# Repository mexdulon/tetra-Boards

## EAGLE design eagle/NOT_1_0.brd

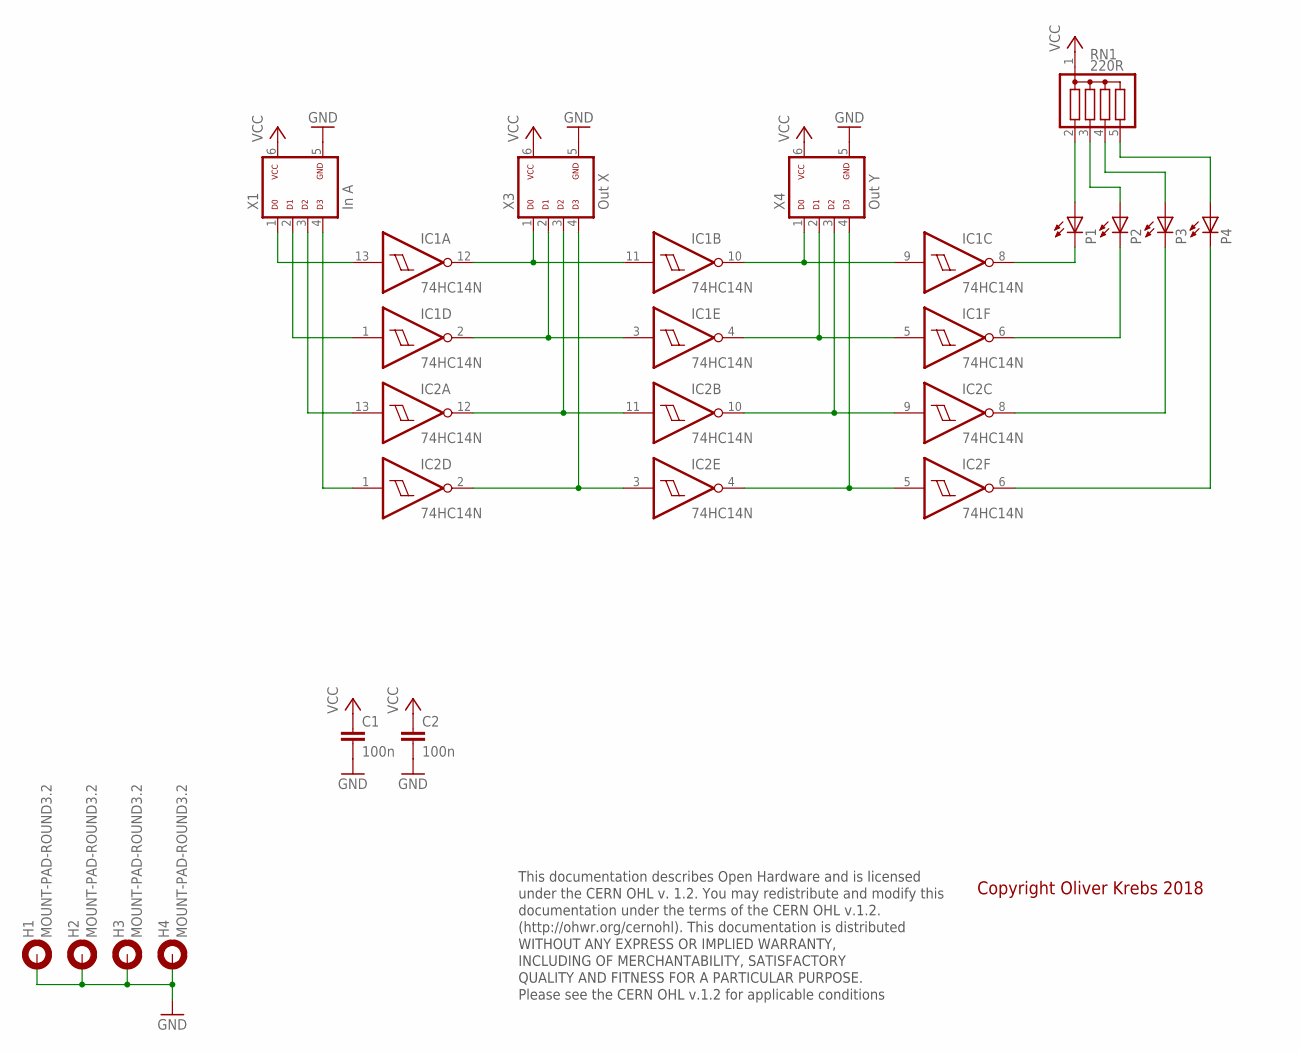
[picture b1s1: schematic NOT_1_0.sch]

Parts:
C1, C2: 100n; C050-025X075
H1, H2, H3, H4: MOUNT-PAD-ROUND3.2; 3,2-PAD
IC1, IC2: 74HC14N; DIL14
P1, P2, P3, P4: LED3MM
RN1: 220R; SIL5
X1: In A; ML-6
X3: Out X; ML-6
X4: Out Y; ML-6

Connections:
GND: C1.2, C2.2, H1.B3,2, H2.B3,2, H3.B3,2, H4.B3,2, IC1.7 (GND), IC2.7 (GND), X1.5, X3.5, X4.5
unnamed: IC1.8 (O), P1.K (C)
unnamed: IC1.6 (O), P2.K (C)
unnamed: IC2.8 (O), P3.K (C)
unnamed: IC2.6 (O), P4.K (C)
unnamed: IC1.9 (I), IC1.10 (O), X4.1
unnamed: IC1.4 (O), IC1.5 (I), X4.2
unnamed: IC2.9 (I), IC2.10 (O), X4.3
unnamed: IC2.4 (O), IC2.5 (I), X4.4
unnamed: IC1.13 (I), X1.1
unnamed: IC1.11 (I), IC1.12 (O), X3.1
unnamed: IC1.2 (O), IC1.3 (I), X3.2
unnamed: IC1.1 (I), X1.2
unnamed: IC2.13 (I), X1.3
unnamed: IC2.11 (I), IC2.12 (O), X3.3
unnamed: IC2.1 (I), X1.4
unnamed: IC2.2 (O), IC2.3 (I), X3.4
unnamed: P1.A, RN1.2
unnamed: P2.A, RN1.3
unnamed: P3.A, RN1.4
unnamed: P4.A, RN1.5
VCC: C1.1, C2.1, IC1.14 (VCC), IC2.14 (VCC), RN1.1, X1.6, X3.6, X4.6

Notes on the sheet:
This documentation describes Open Hardware and is licensed under the CERN OHL v. 1.2. You may redistribute and modify this documentation under the terms of the CERN OHL v.1.2. (http://ohwr.org/cernohl). This documentation is distributed WITHOUT ANY EXPRESS OR IMPLIED WARRANTY, INCLUDING OF MERCHANT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
Copyright Oliver Krebs 2018

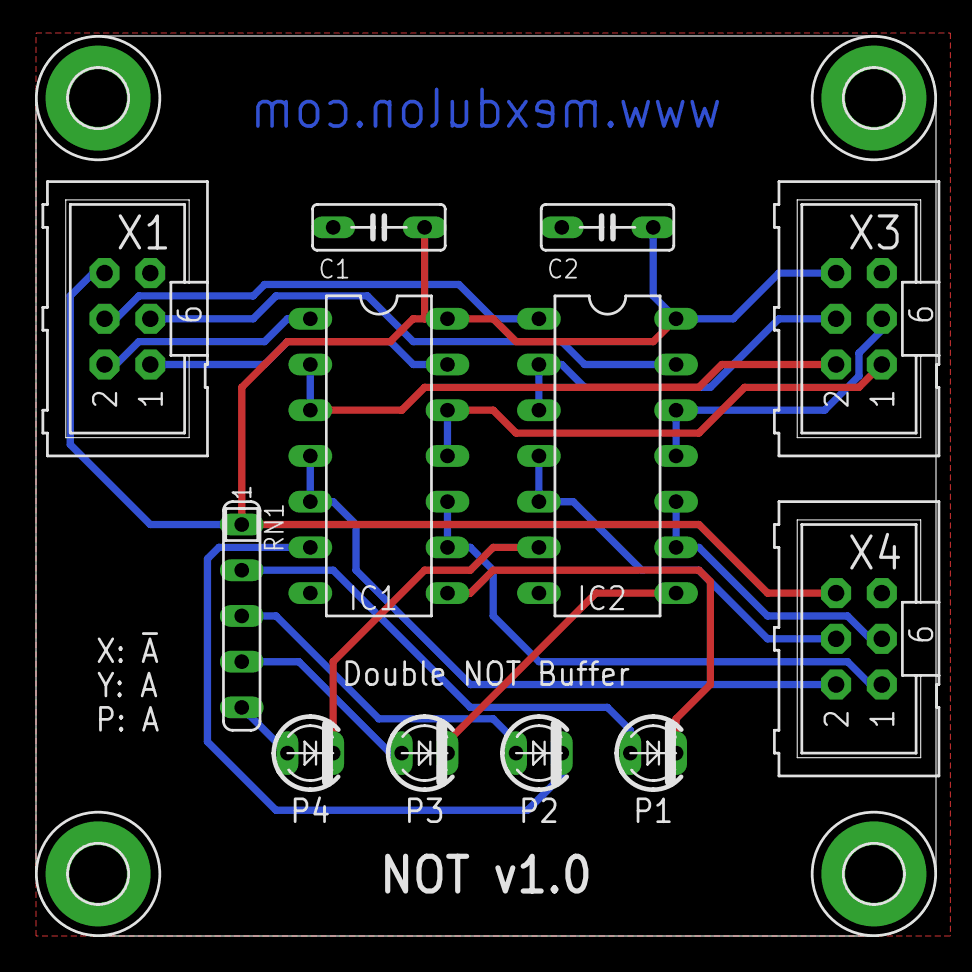
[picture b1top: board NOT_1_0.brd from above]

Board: 2 copper layers, 50.0 x 50.0 mm, 16 parts (0 on the bottom side), 22 nets.

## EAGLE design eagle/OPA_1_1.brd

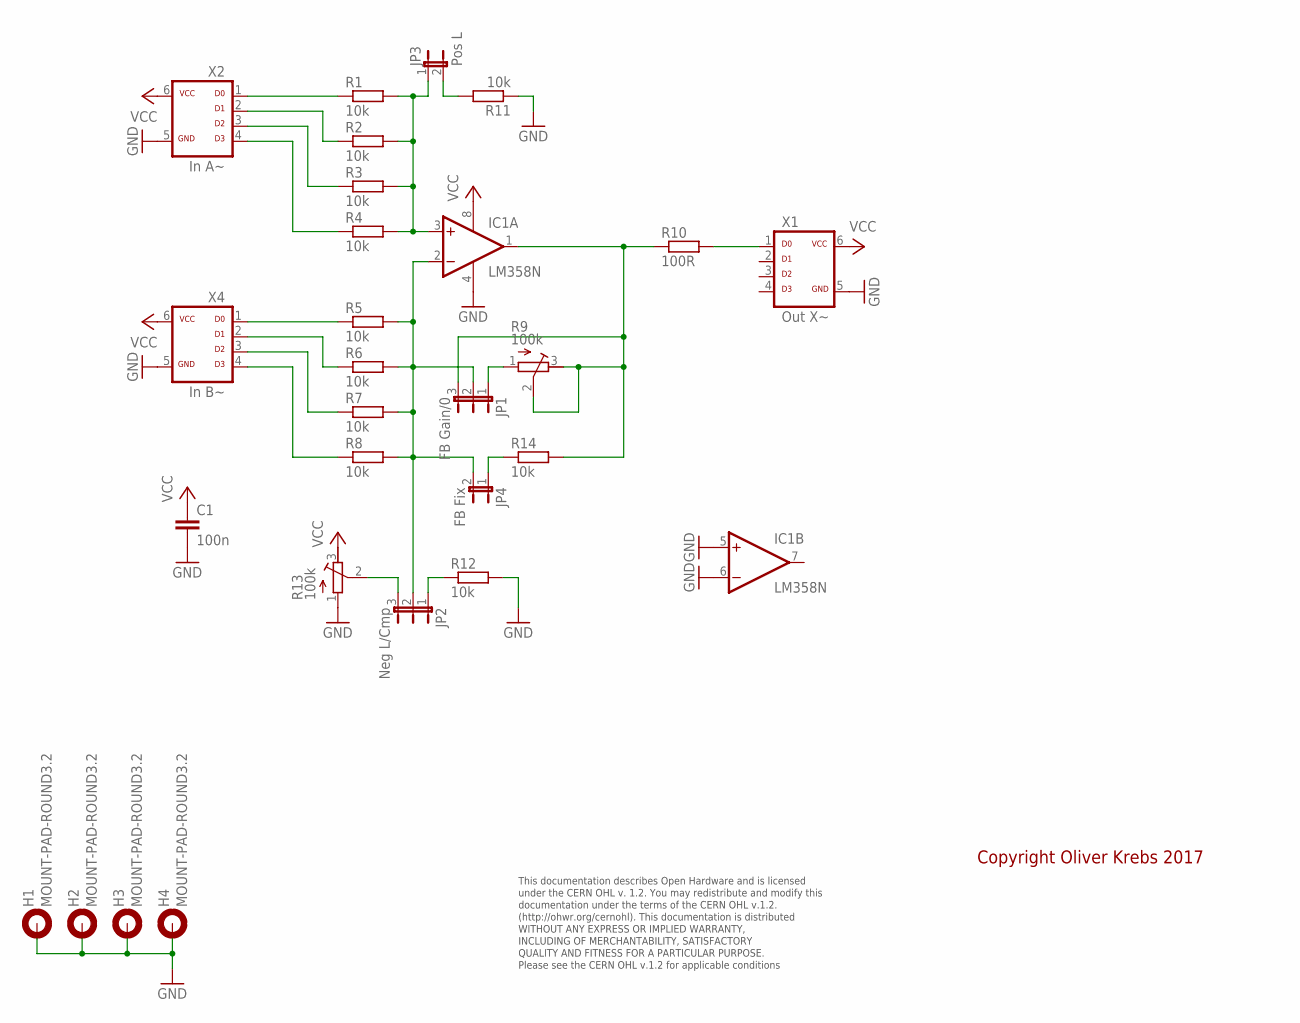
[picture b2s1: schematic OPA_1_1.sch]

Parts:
C1: 100n; C050-025X075
H1, H2, H3, H4: MOUNT-PAD-ROUND3.2; 3,2-PAD
IC1: LM358N; DIL08
JP1: FB Gain/0; JP2-U
JP2: Neg L/Cmp; JP2-U
JP3: Pos L; JP1
JP4: FB Fix; JP1
R1, R2, R3, R4, R5, R6, R7, R8, R11, R12, R14: 10k; 0207/10
R9, R13: 100k; ACP-6L
R10: 100R; 0207/10
X1: Out X~; ML-6
X2: In A~; ML-6
X4: In B~; ML-6

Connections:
GND: C1.2, H1.B3,2, H2.B3,2, H3.B3,2, H4.B3,2, IC1.4 (V-), IC1.5 (+IN), IC1.6 (-IN), R11.1, R12.2, R13.1 (A), X1.5, X2.5, X4.5
unnamed: JP2.1, R12.1
unnamed: IC1.2 (-IN), JP1.2, JP2.2, JP4.2, R5.2, R6.2, R7.2, R8.2
unnamed: R1.1, X2.1
unnamed: R2.1, X2.2
unnamed: IC1.3 (+IN), JP3.1, R1.2, R2.2, R3.2, R4.2
unnamed: R10.2, X1.1
unnamed: JP1.1, R9.1 (A)
unnamed: R3.1, X2.3
unnamed: R4.1, X2.4
unnamed: R5.1, X4.1
unnamed: R6.1, X4.2
unnamed: R7.1, X4.3
unnamed: R8.1, X4.4
unnamed: JP2.3, R13.2 (S)
unnamed: IC1.1 (OUT), JP1.3, R9.2 (S), R9.3 (E), R10.1, R14.2
unnamed: JP3.2, R11.2
unnamed: JP4.1, R14.1
VCC: C1.1, IC1.8 (V+), R13.3 (E), X1.6, X2.6, X4.6

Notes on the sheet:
This documentation describes Open Hardware and is licensed under the CERN OHL v. 1.2. You may redistribute and modify this documentation under the terms of the CERN OHL v.1.2. (http://ohwr.org/cernohl). This documentation is distributed WITHOUT ANY EXPRESS OR IMPLIED WARRANTY, INCLUDING OF MERCHANT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
Copyright Oliver Krebs 2017

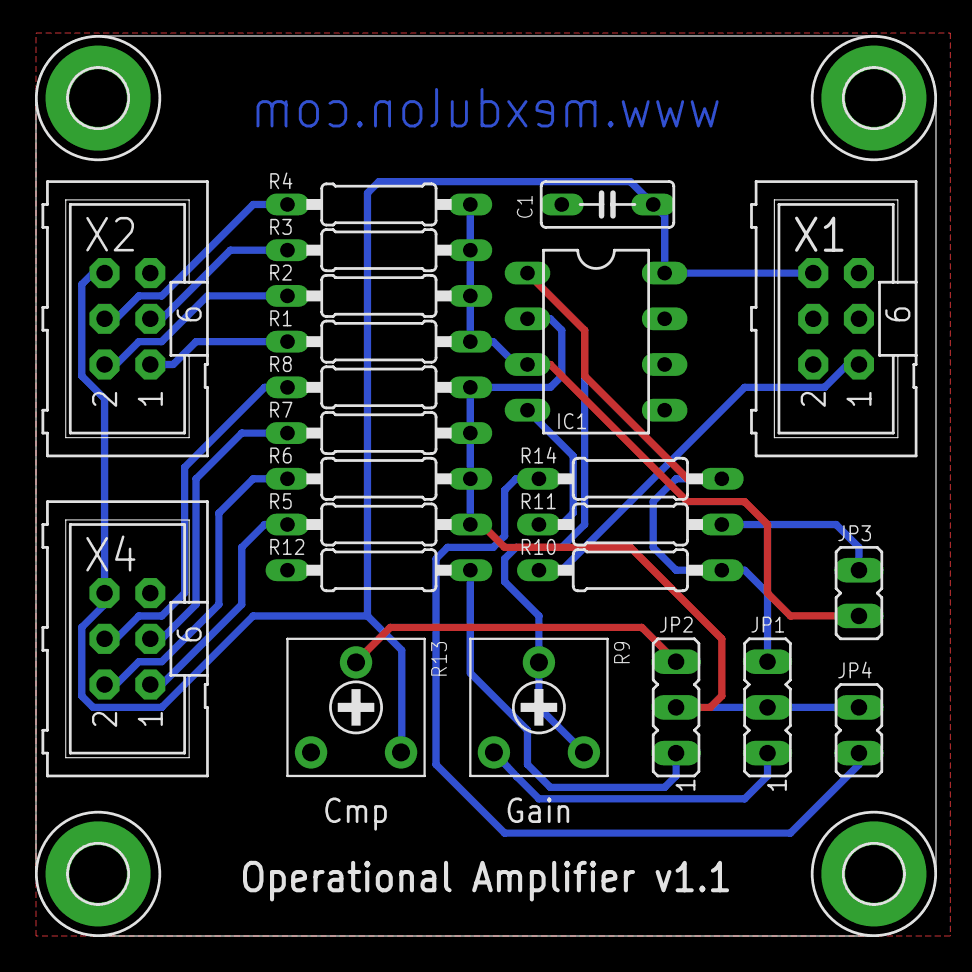
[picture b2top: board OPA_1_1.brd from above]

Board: 2 copper layers, 50.0 x 50.0 mm, 27 parts (0 on the bottom side), 19 nets.

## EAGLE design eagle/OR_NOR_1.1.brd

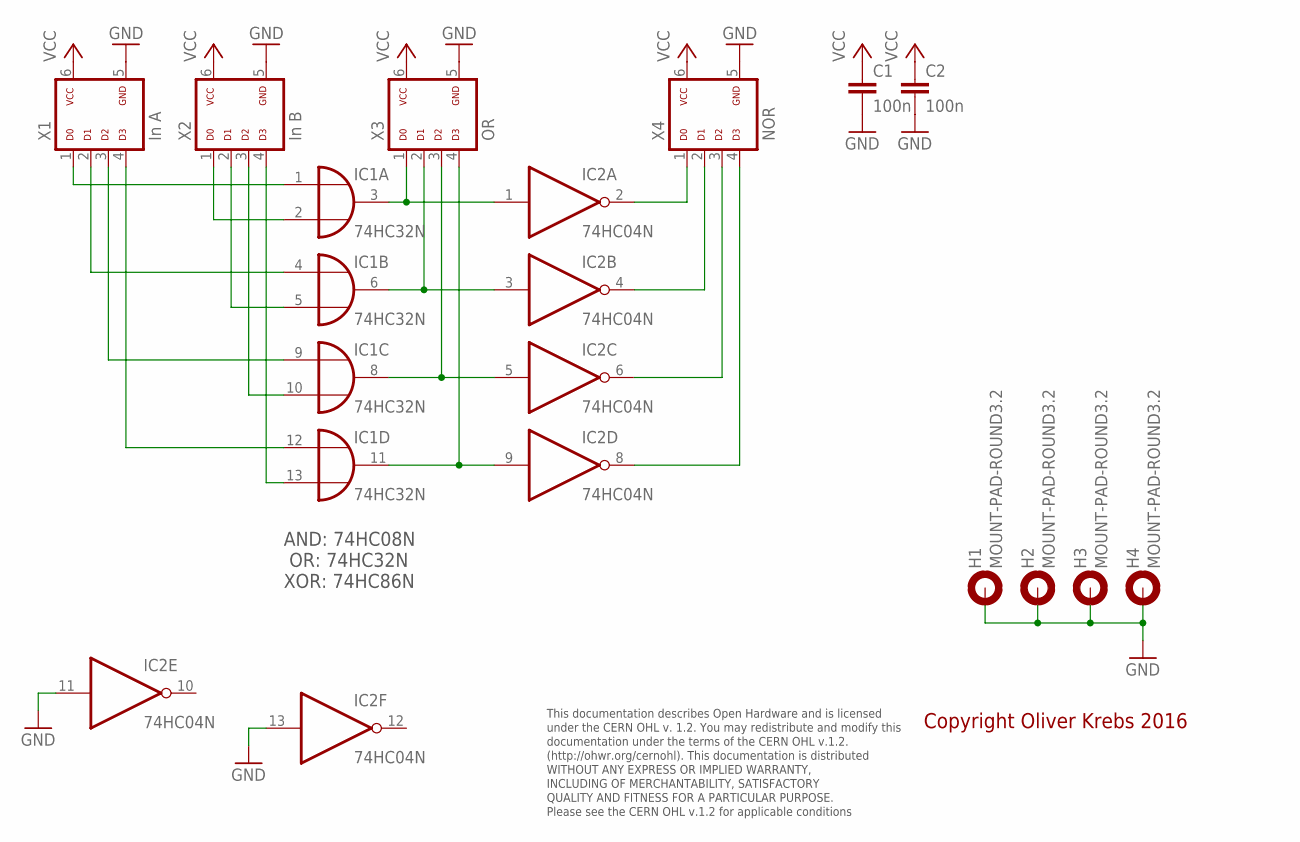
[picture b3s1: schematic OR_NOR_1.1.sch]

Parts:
C1, C2: 100n; C050-025X075
H1, H2, H3, H4: MOUNT-PAD-ROUND3.2; 3,2-PAD
IC1: 74HC32N; DIL14
IC2: 74HC04N; DIL14
X1: In A; ML-6
X2: In B; ML-6
X3: OR; ML-6
X4: NOR; ML-6

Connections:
GND: C1.2, C2.2, H1.B3,2, H2.B3,2, H3.B3,2, H4.B3,2, IC1.7 (GND), IC2.7 (GND), IC2.11 (I), IC2.13 (I), X1.5, X2.5, X3.5, X4.5
unnamed: IC1.3 (O), IC2.1 (I), X3.1
unnamed: IC1.6 (O), IC2.3 (I), X3.2
unnamed: IC1.8 (O), IC2.5 (I), X3.3
unnamed: IC1.11 (O), IC2.9 (I), X3.4
unnamed: IC2.2 (O), X4.1
unnamed: IC2.4 (O), X4.2
unnamed: IC2.6 (O), X4.3
unnamed: IC2.8 (O), X4.4
unnamed: IC1.1 (I0), X1.1
unnamed: IC1.2 (I1), X2.1
unnamed: IC1.5 (I1), X2.2
unnamed: IC1.4 (I0), X1.2
unnamed: IC1.9 (I0), X1.3
unnamed: IC1.10 (I1), X2.3
unnamed: IC1.12 (I0), X1.4
unnamed: IC1.13 (I1), X2.4
VCC: C1.1, C2.1, IC1.14 (VCC), IC2.14 (VCC), X1.6, X2.6, X3.6, X4.6

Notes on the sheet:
AND: 74HC08N OR: 74HC32N XOR: 74HC86N
This documentation describes Open Hardware and is licensed under the CERN OHL v. 1.2. You may redistribute and modify this documentation under the terms of the CERN OHL v.1.2. (http://ohwr.org/cernohl). This documentation is distributed WITHOUT ANY EXPRESS OR IMPLIED WARRANTY, INCLUDING OF MERCHANT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
Copyright Oliver Krebs 2016

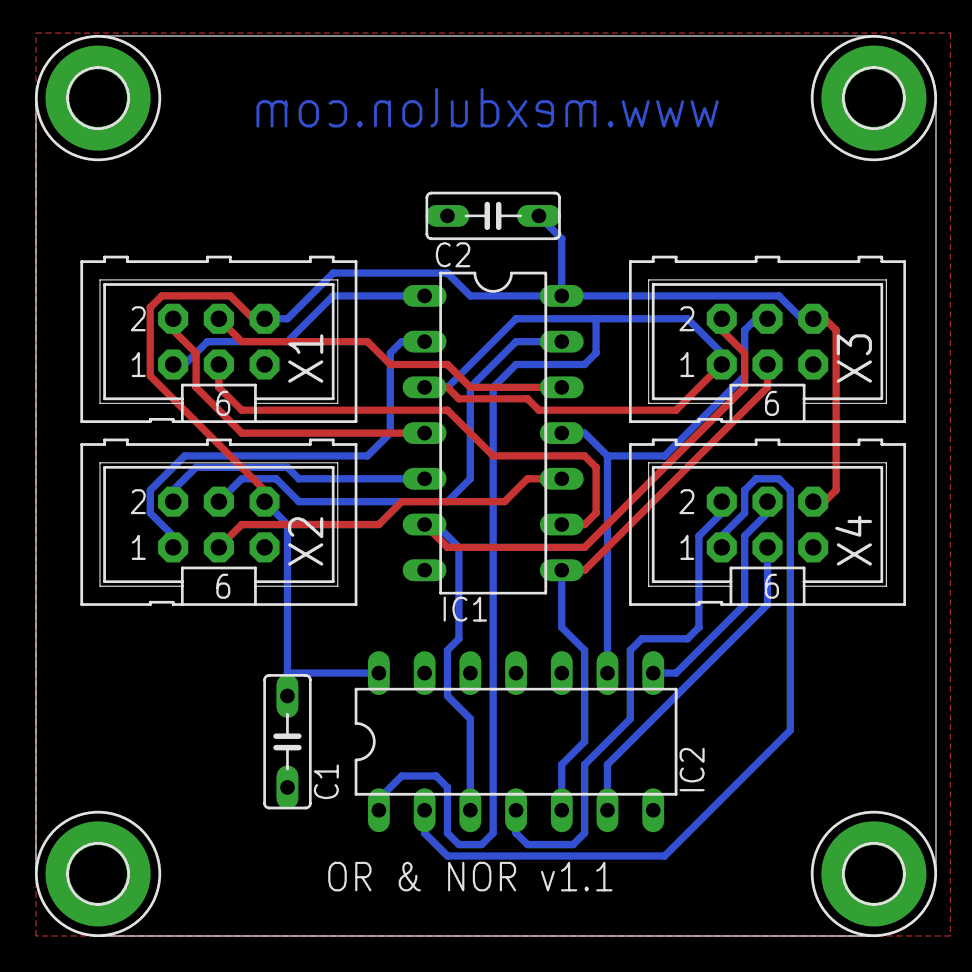
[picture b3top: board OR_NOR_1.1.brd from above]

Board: 2 copper layers, 50.0 x 50.0 mm, 12 parts (0 on the bottom side), 18 nets.

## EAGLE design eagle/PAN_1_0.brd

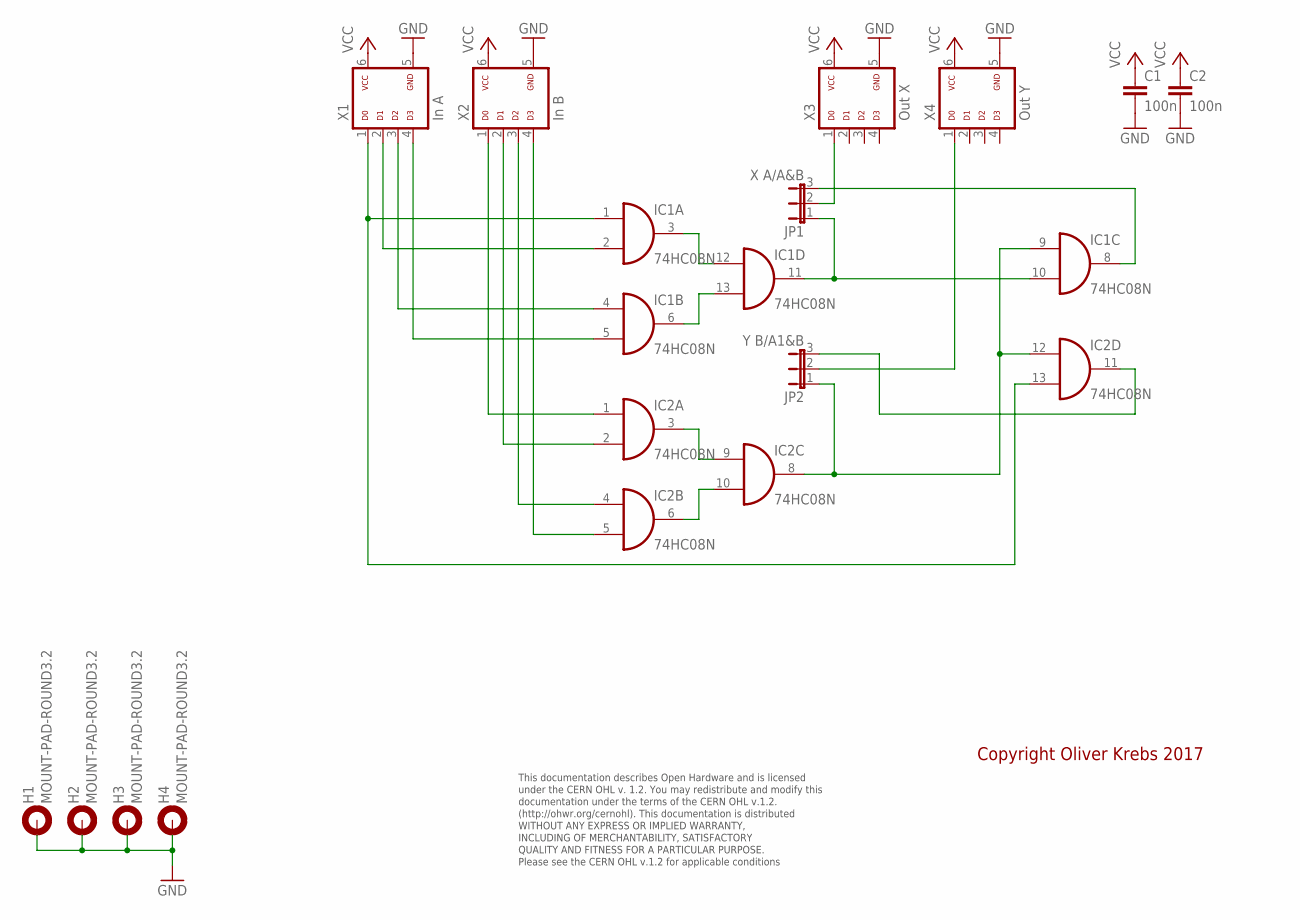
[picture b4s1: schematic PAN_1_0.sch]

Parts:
C1, C2: 100n; C050-025X075
H1, H2, H3, H4: MOUNT-PAD-ROUND3.2; 3,2-PAD
IC1, IC2: 74HC08N; DIL14
JP1: X A/A&B; JP2-U
JP2: Y B/A1&B; JP2-U
X1: In A; ML-6
X2: In B; ML-6
X3: Out X; ML-6
X4: Out Y; ML-6

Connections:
GND: C1.2, C2.2, H1.B3,2, H2.B3,2, H3.B3,2, H4.B3,2, IC1.7 (GND), IC2.7 (GND), X1.5, X2.5, X3.5, X4.5
unnamed: IC1.1 (I0), IC2.13 (I1), X1.1
unnamed: IC1.4 (I0), X1.3
unnamed: IC1.3 (O), IC1.12 (I0)
unnamed: IC1.5 (I1), X1.4
unnamed: IC1.2 (I1), X1.2
unnamed: IC1.6 (O), IC1.13 (I1)
unnamed: IC1.10 (I1), IC1.11 (O), JP1.1
unnamed: IC2.1 (I0), X2.1
unnamed: IC2.2 (I1), X2.2
unnamed: IC2.4 (I0), X2.3
unnamed: IC2.5 (I1), X2.4
unnamed: IC2.3 (O), IC2.9 (I0)
unnamed: IC2.6 (O), IC2.10 (I1)
unnamed: IC1.9 (I0), IC2.8 (O), IC2.12 (I0), JP2.1
unnamed: JP1.2, X3.1
unnamed: IC1.8 (O), JP1.3
unnamed: IC2.11 (O), JP2.3
unnamed: JP2.2, X4.1
VCC: C1.1, C2.1, IC1.14 (VCC), IC2.14 (VCC), X1.6, X2.6, X3.6, X4.6

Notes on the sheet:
This documentation describes Open Hardware and is licensed under the CERN OHL v. 1.2. You may redistribute and modify this documentation under the terms of the CERN OHL v.1.2. (http://ohwr.org/cernohl). This documentation is distributed WITHOUT ANY EXPRESS OR IMPLIED WARRANTY, INCLUDING OF MERCHANT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
Copyright Oliver Krebs 2017

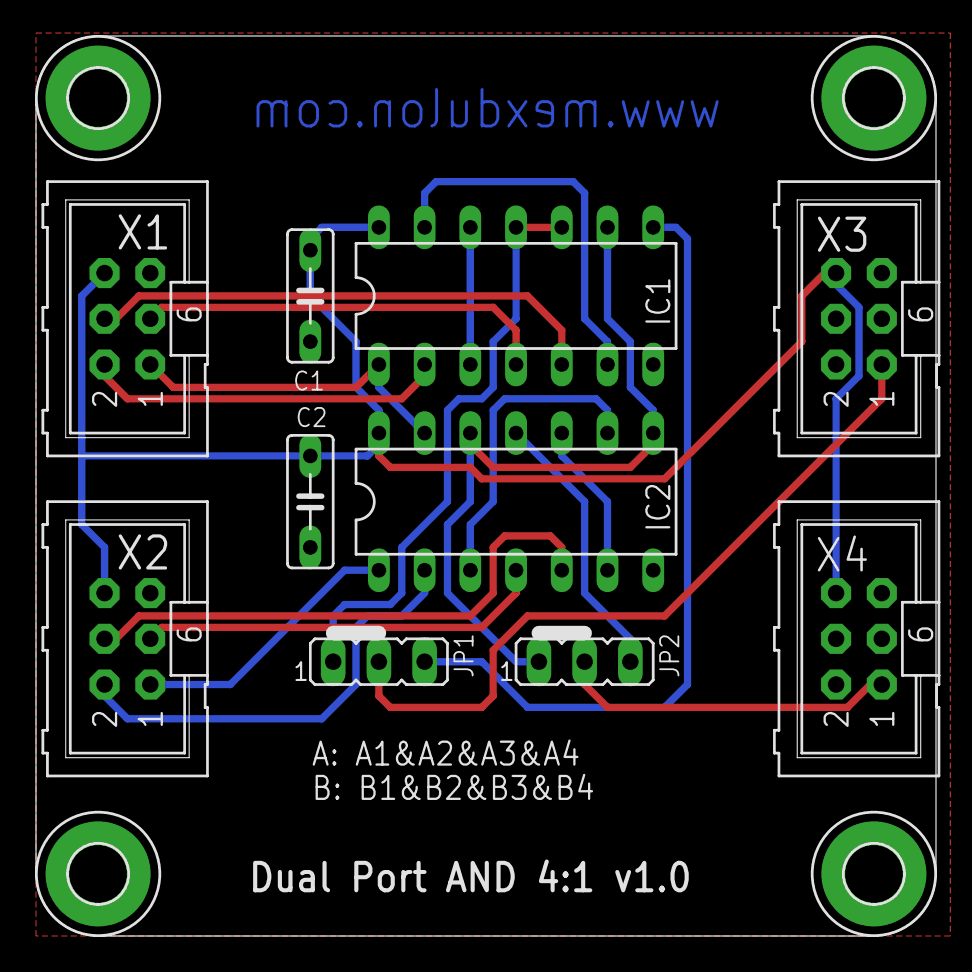
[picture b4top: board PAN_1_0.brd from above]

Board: 2 copper layers, 50.0 x 50.0 mm, 14 parts (0 on the bottom side), 20 nets.

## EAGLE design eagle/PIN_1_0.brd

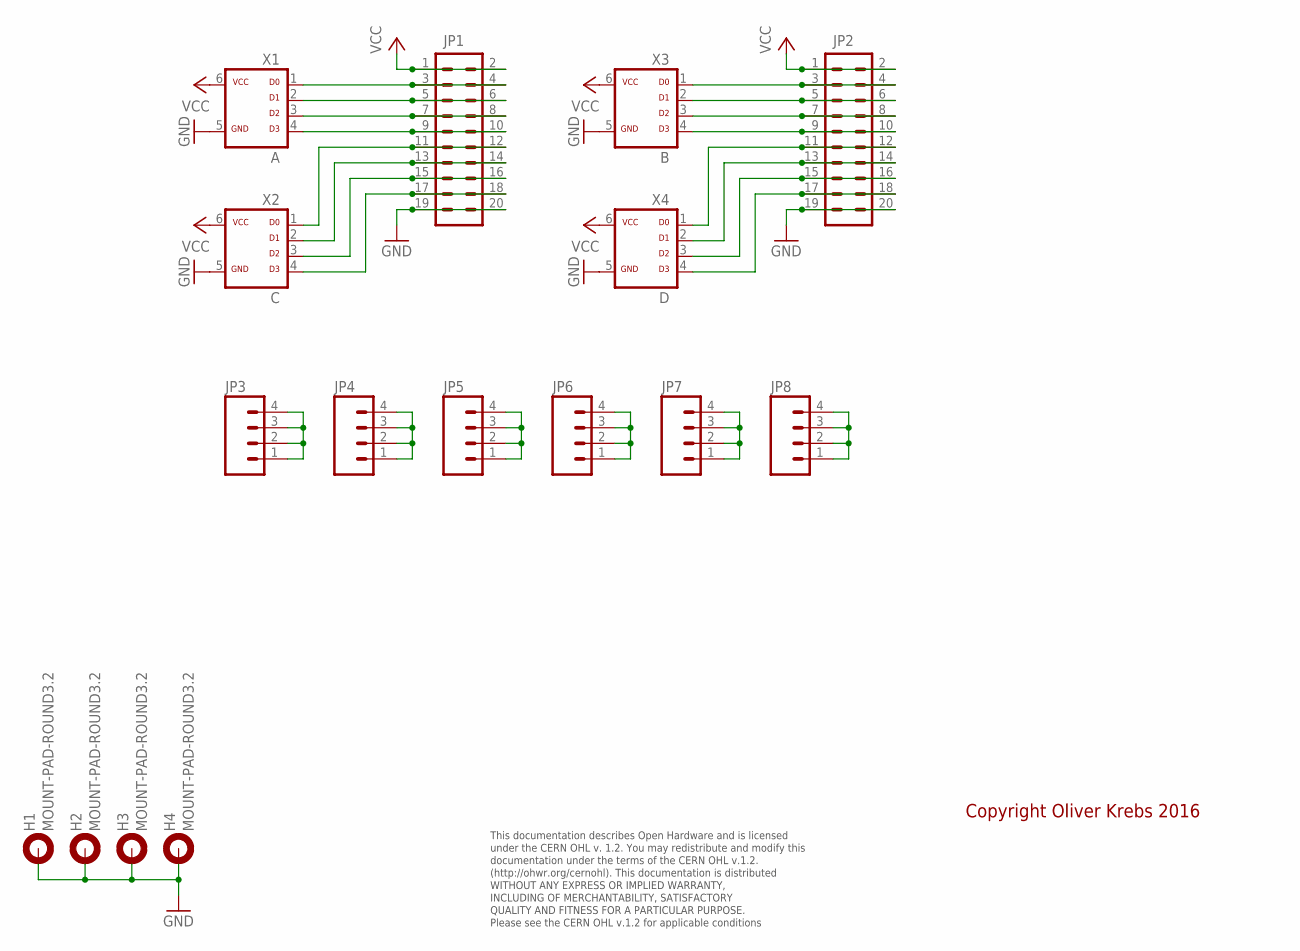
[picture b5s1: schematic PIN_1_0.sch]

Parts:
H1, H2, H3, H4: MOUNT-PAD-ROUND3.2; 3,2-PAD
JP1, JP2: M10X2; 2X10
JP3, JP4, JP5, JP6, JP7, JP8: M04PTH; 1X04
X1: A; ML-6
X2: C; ML-6
X3: B; ML-6
X4: D; ML-6

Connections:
GND: H1.B3,2, H2.B3,2, H3.B3,2, H4.B3,2, JP1.19, JP1.20, JP2.19, JP2.20, X1.5, X2.5, X3.5, X4.5
unnamed: JP2.3, JP2.4, X3.1
unnamed: JP2.5, JP2.6, X3.2
unnamed: JP2.7, JP2.8, X3.3
unnamed: JP2.9, JP2.10, X3.4
unnamed: JP2.11, JP2.12, X4.1
unnamed: JP2.13, JP2.14, X4.2
unnamed: JP2.15, JP2.16, X4.3
unnamed: JP2.17, JP2.18, X4.4
unnamed: JP1.3, JP1.4, X1.1
unnamed: JP1.5, JP1.6, X1.2
unnamed: JP1.7, JP1.8, X1.3
unnamed: JP1.9, JP1.10, X1.4
unnamed: JP1.11, JP1.12, X2.1
unnamed: JP1.13, JP1.14, X2.2
unnamed: JP1.15, JP1.16, X2.3
unnamed: JP1.17, JP1.18, X2.4
unnamed: JP3.1, JP3.2, JP3.3, JP3.4
unnamed: JP4.1, JP4.2, JP4.3, JP4.4
unnamed: JP5.1, JP5.2, JP5.3, JP5.4
unnamed: JP6.1, JP6.2, JP6.3, JP6.4
unnamed: JP7.1, JP7.2, JP7.3, JP7.4
unnamed: JP8.1, JP8.2, JP8.3, JP8.4
VCC: JP1.1, JP1.2, JP2.1, JP2.2, X1.6, X2.6, X3.6, X4.6

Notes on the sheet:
This documentation describes Open Hardware and is licensed under the CERN OHL v. 1.2. You may redistribute and modify this documentation under the terms of the CERN OHL v.1.2. (http://ohwr.org/cernohl). This documentation is distributed WITHOUT ANY EXPRESS OR IMPLIED WARRANTY, INCLUDING OF MERCHANT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
Copyright Oliver Krebs 2016

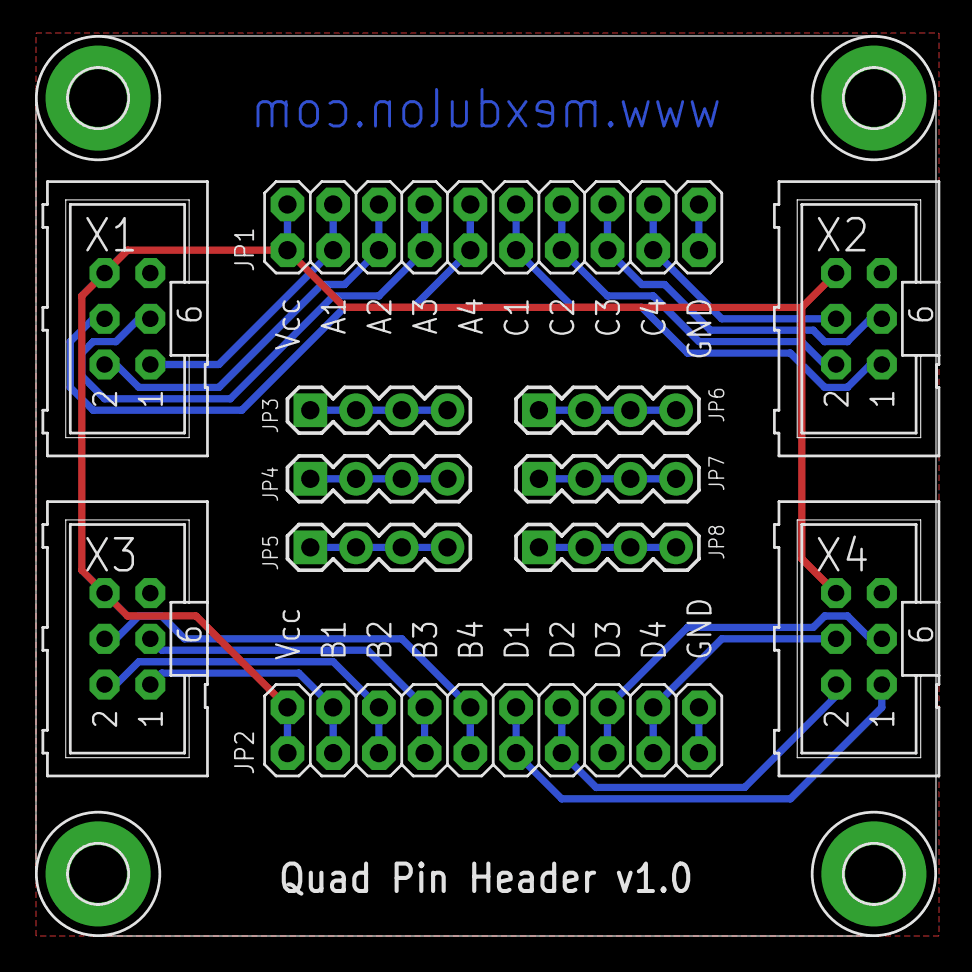
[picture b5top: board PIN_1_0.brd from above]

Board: 2 copper layers, 50.0 x 50.0 mm, 16 parts (0 on the bottom side), 24 nets.

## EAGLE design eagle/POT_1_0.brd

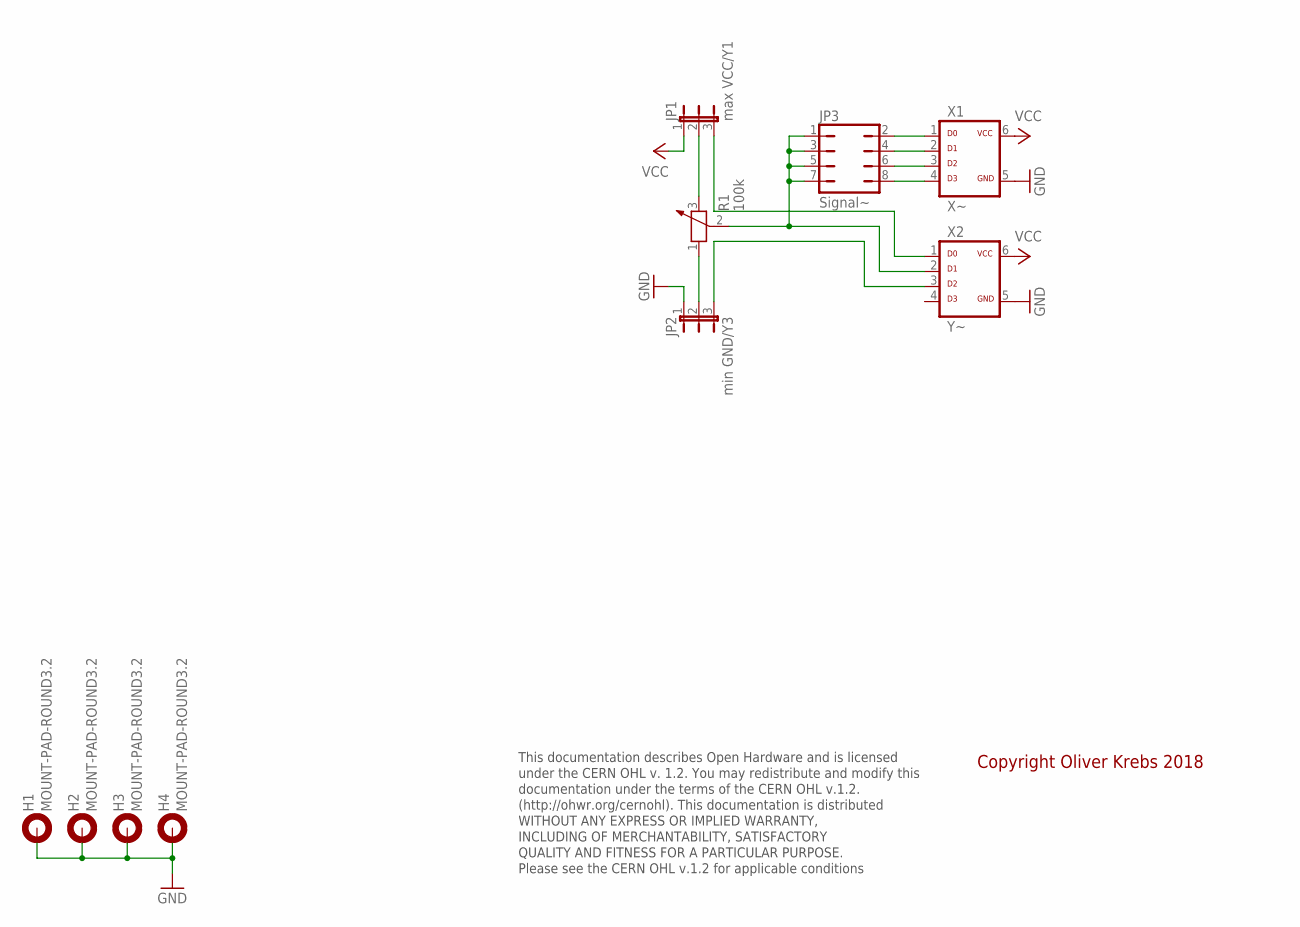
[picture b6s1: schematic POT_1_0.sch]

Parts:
H1, H2, H3, H4: MOUNT-PAD-ROUND3.2; 3,2-PAD
JP1: max VCC/Y1; JP2-U
JP2: min GND/Y3; JP2-U
JP3: Signal~; JP4Q
R1: 100k; RK09K113
X1: X~; ML-6
X2: Y~; ML-6

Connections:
GND: H1.B3,2, H2.B3,2, H3.B3,2, H4.B3,2, JP2.1, X1.5, X2.5
unnamed: JP3.2, X1.1
unnamed: JP1.3, X2.1
unnamed: JP2.3, X2.3
unnamed: JP3.4, X1.2
unnamed: JP1.2, R1.3 (2)
unnamed: JP2.2, R1.1
unnamed: JP3.6, X1.3
unnamed: JP3.8, X1.4
unnamed: JP3.1, JP3.3, JP3.5, JP3.7, R1.2 (3), X2.2
VCC: JP1.1, X1.6, X2.6

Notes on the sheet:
This documentation describes Open Hardware and is licensed under the CERN OHL v. 1.2. You may redistribute and modify this documentation under the terms of the CERN OHL v.1.2. (http://ohwr.org/cernohl). This documentation is distributed WITHOUT ANY EXPRESS OR IMPLIED WARRANTY, INCLUDING OF MERCHANT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
Copyright Oliver Krebs 2018

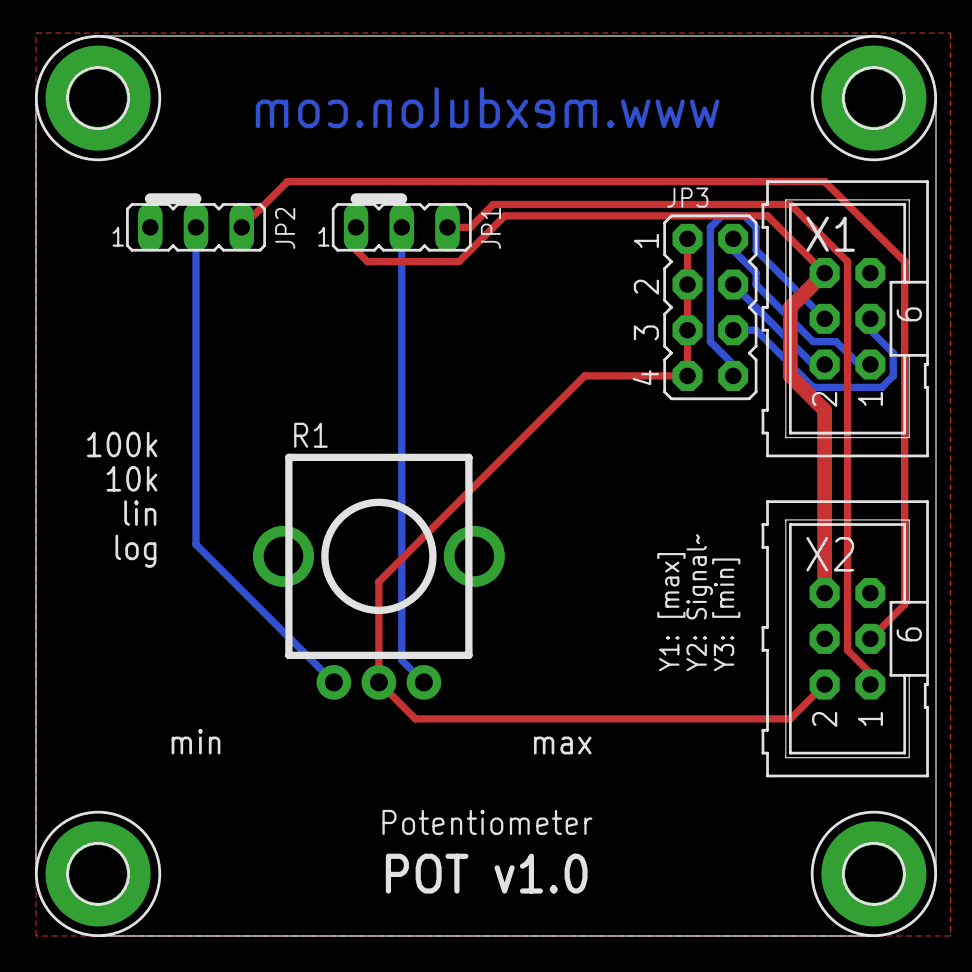
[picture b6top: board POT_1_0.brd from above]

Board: 2 copper layers, 50.0 x 50.0 mm, 10 parts (0 on the bottom side), 11 nets.

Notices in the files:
eagle/NOT_1_0.brd:
Licensed under CERN OHL v.1.2
parts and their libraries:
SparkFun-Connectors: Licensing: Creative Commons ShareAlike 4.0 International - https://creativecommons.org/licenses/by-sa/4.0
